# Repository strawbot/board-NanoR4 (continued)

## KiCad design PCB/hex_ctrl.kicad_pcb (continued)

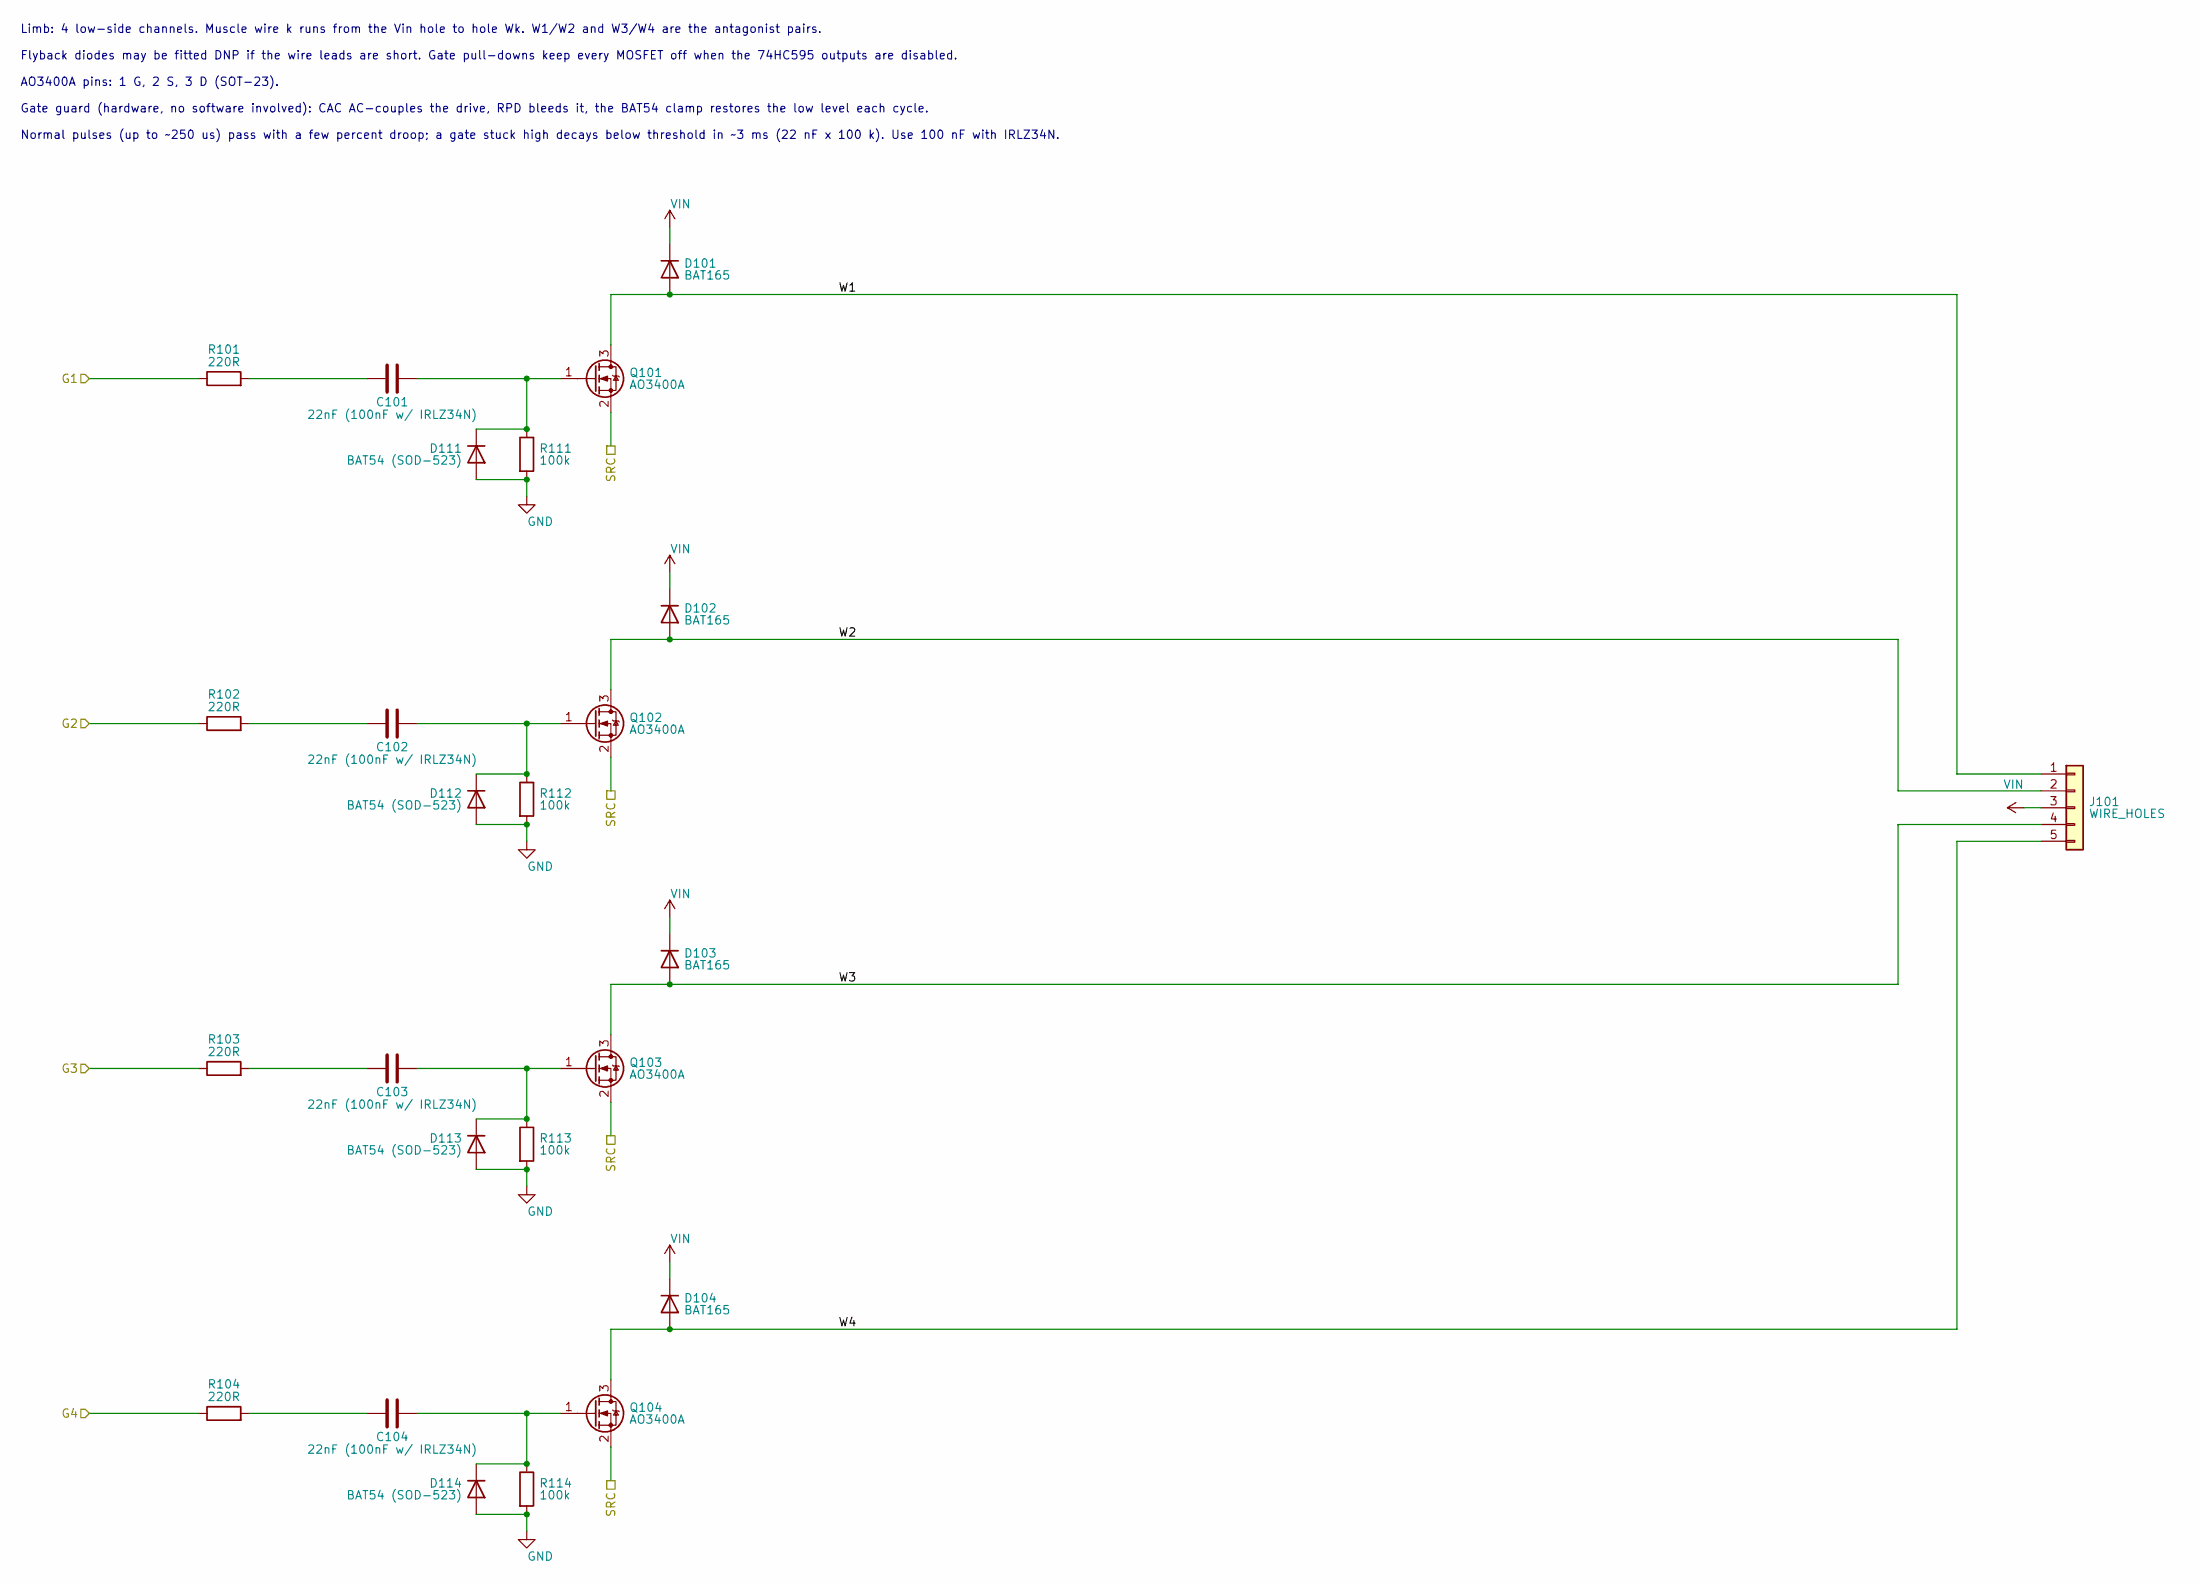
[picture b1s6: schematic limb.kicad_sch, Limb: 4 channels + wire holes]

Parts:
C101, C102, C103, C104: 22nF (100nF w/ IRLZ34N); C_0402_1005Metric
D101, D102, D103, D104: BAT165; D_SOD-323
D111, D112, D113, D114: BAT54 (SOD-523); D_SOD-523
J101: WIRE_HOLES; PinHeader_1x05_P2.54mm_Vertical
Q101, Q102, Q103, Q104: AO3400A; SOT-23
R101, R102, R103, R104: 220R; R_0402_1005Metric
R111, R112, R113, R114: 100k; R_0402_1005Metric

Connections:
/group_A/SRC: Q101.2 (S), Q102.2 (S), Q103.2 (S), Q104.2 (S); also elsewhere on the board
/group_A/limb_a/W1: D101.2 (A), J101.1, Q101.3 (D)
/group_A/limb_a/W2: D102.2 (A), J101.2, Q102.3 (D)
/group_A/limb_a/W3: D103.2 (A), J101.4, Q103.3 (D)
/group_A/limb_a/W4: D104.2 (A), J101.5, Q104.3 (D)
GND: D111.2 (A), D112.2 (A), D113.2 (A), D114.2 (A), R111.2, R112.2, R113.2, R114.2; also elsewhere on the board
G_A1: R101.1; also elsewhere on the board
G_A2: R102.1; also elsewhere on the board
G_A3: R103.1; also elsewhere on the board
G_A4: R104.1; also elsewhere on the board
unnamed: C101.1, R101.2
unnamed: C102.1, R102.2
unnamed: C103.1, R103.2
unnamed: C104.1, R104.2
unnamed: C101.2, D111.1 (K), Q101.1 (G), R111.1
unnamed: C102.2, D112.1 (K), Q102.1 (G), R112.1
unnamed: C103.2, D113.1 (K), Q103.1 (G), R113.1
unnamed: C104.2, D114.1 (K), Q104.1 (G), R114.1
VIN: D101.1 (K), D102.1 (K), D103.1 (K), D104.1 (K), J101.3; also elsewhere on the board

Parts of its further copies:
C201, C202, C203, C204, C301, C302, C303, C304, C401, C402, C403, C404, C501, C502, C503, C504, C601, C602, C603, C604: 22nF (100nF w/ IRLZ34N); C_0402_1005Metric
D201, D202, D203, D204, D301, D302, D303, D304, D401, D402, D403, D404, D501, D502, D503, D504, D601, D602, D603, D604: BAT165; D_SOD-323
D211, D212, D213, D214, D311, D312, D313, D314, D411, D412, D413, D414, D511, D512, D513, D514, D611, D612, D613, D614: BAT54 (SOD-523); D_SOD-523
J201, J301, J401, J501, J601: WIRE_HOLES; PinHeader_1x05_P2.54mm_Vertical
Q201, Q202, Q203, Q204, Q301, Q302, Q303, Q304, Q401, Q402, Q403, Q404, Q501, Q502, Q503, Q504, Q601, Q602, Q603, Q604: AO3400A; SOT-23
R201, R202, R203, R204, R301, R302, R303, R304, R401, R402, R403, R404, R501, R502, R503, R504, R601, R602, R603, R604: 220R; R_0402_1005Metric
R211, R212, R213, R214, R311, R312, R313, R314, R411, R412, R413, R414, R511, R512, R513, R514, R611, R612, R613, R614: 100k; R_0402_1005Metric

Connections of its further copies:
/group_A/SRC: Q201.2 (S), Q202.2 (S), Q203.2 (S), Q204.2 (S); also elsewhere on the board
/group_A/limb_b/W1: D201.2 (A), J201.1, Q201.3 (D)
/group_A/limb_b/W2: D202.2 (A), J201.2, Q202.3 (D)
/group_A/limb_b/W3: D203.2 (A), J201.4, Q203.3 (D)
/group_A/limb_b/W4: D204.2 (A), J201.5, Q204.3 (D)
/group_B/SRC: Q301.2 (S), Q302.2 (S), Q303.2 (S), Q304.2 (S), Q401.2 (S), Q402.2 (S), Q403.2 (S), Q404.2 (S); also elsewhere on the board
/group_B/limb_a/W1: D301.2 (A), J301.1, Q301.3 (D)
/group_B/limb_a/W2: D302.2 (A), J301.2, Q302.3 (D)
/group_B/limb_a/W3: D303.2 (A), J301.4, Q303.3 (D)
/group_B/limb_a/W4: D304.2 (A), J301.5, Q304.3 (D)
/group_B/limb_b/W1: D401.2 (A), J401.1, Q401.3 (D)
/group_B/limb_b/W2: D402.2 (A), J401.2, Q402.3 (D)
/group_B/limb_b/W3: D403.2 (A), J401.4, Q403.3 (D)
/group_B/limb_b/W4: D404.2 (A), J401.5, Q404.3 (D)
/group_C/SRC: Q501.2 (S), Q502.2 (S), Q503.2 (S), Q504.2 (S), Q601.2 (S), Q602.2 (S), Q603.2 (S), Q604.2 (S); also elsewhere on the board
/group_C/limb_a/W1: D501.2 (A), J501.1, Q501.3 (D)
/group_C/limb_a/W2: D502.2 (A), J501.2, Q502.3 (D)
/group_C/limb_a/W3: D503.2 (A), J501.4, Q503.3 (D)
/group_C/limb_a/W4: D504.2 (A), J501.5, Q504.3 (D)
/group_C/limb_b/W1: D601.2 (A), J601.1, Q601.3 (D)
/group_C/limb_b/W2: D602.2 (A), J601.2, Q602.3 (D)
/group_C/limb_b/W3: D603.2 (A), J601.4, Q603.3 (D)
/group_C/limb_b/W4: D604.2 (A), J601.5, Q604.3 (D)
GND: D211.2 (A), D212.2 (A), D213.2 (A), D214.2 (A), D311.2 (A), D312.2 (A), D313.2 (A), D314.2 (A), D411.2 (A), D412.2 (A), D413.2 (A), D414.2 (A), D511.2 (A), D512.2 (A), D513.2 (A), D514.2 (A), D611.2 (A), D612.2 (A), D613.2 (A), D614.2 (A), R211.2, R212.2, R213.2, R214.2, R311.2, R312.2, R313.2, R314.2, R411.2, R412.2, R413.2, R414.2, R511.2, R512.2, R513.2, R514.2, R611.2, R612.2, R613.2, R614.2; also elsewhere on the board
G_A5: R201.1; also elsewhere on the board
G_A6: R202.1; also elsewhere on the board
G_A7: R203.1; also elsewhere on the board
G_A8: R204.1; also elsewhere on the board
G_B1: R301.1; also elsewhere on the board
G_B2: R302.1; also elsewhere on the board
G_B3: R303.1; also elsewhere on the board
G_B4: R304.1; also elsewhere on the board
G_B5: R401.1; also elsewhere on the board
G_B6: R402.1; also elsewhere on the board
G_B7: R403.1; also elsewhere on the board
G_B8: R404.1; also elsewhere on the board
G_C1: R501.1; also elsewhere on the board
G_C2: R502.1; also elsewhere on the board
G_C3: R503.1; also elsewhere on the board
G_C4: R504.1; also elsewhere on the board
G_C5: R601.1; also elsewhere on the board
G_C6: R602.1; also elsewhere on the board
G_C7: R603.1; also elsewhere on the board
G_C8: R604.1; also elsewhere on the board
unnamed: C201.1, R201.2
unnamed: C202.1, R202.2
unnamed: C203.1, R203.2
unnamed: C204.1, R204.2
unnamed: C301.1, R301.2
unnamed: C302.1, R302.2
unnamed: C303.1, R303.2
unnamed: C304.1, R304.2
unnamed: C401.1, R401.2
unnamed: C402.1, R402.2
unnamed: C403.1, R403.2
unnamed: C404.1, R404.2
unnamed: C501.1, R501.2
unnamed: C502.1, R502.2
unnamed: C503.1, R503.2
unnamed: C504.1, R504.2
unnamed: C601.1, R601.2
unnamed: C602.1, R602.2
unnamed: C603.1, R603.2
unnamed: C604.1, R604.2
unnamed: C201.2, D211.1 (K), Q201.1 (G), R211.1
unnamed: C202.2, D212.1 (K), Q202.1 (G), R212.1
unnamed: C203.2, D213.1 (K), Q203.1 (G), R213.1
unnamed: C204.2, D214.1 (K), Q204.1 (G), R214.1
unnamed: C301.2, D311.1 (K), Q301.1 (G), R311.1
unnamed: C302.2, D312.1 (K), Q302.1 (G), R312.1
unnamed: C303.2, D313.1 (K), Q303.1 (G), R313.1
unnamed: C304.2, D314.1 (K), Q304.1 (G), R314.1
unnamed: C401.2, D411.1 (K), Q401.1 (G), R411.1
unnamed: C402.2, D412.1 (K), Q402.1 (G), R412.1
unnamed: C403.2, D413.1 (K), Q403.1 (G), R413.1
unnamed: C404.2, D414.1 (K), Q404.1 (G), R414.1
unnamed: C501.2, D511.1 (K), Q501.1 (G), R511.1
unnamed: C502.2, D512.1 (K), Q502.1 (G), R512.1
unnamed: C503.2, D513.1 (K), Q503.1 (G), R513.1
unnamed: C504.2, D514.1 (K), Q504.1 (G), R514.1
unnamed: C601.2, D611.1 (K), Q601.1 (G), R611.1
unnamed: C602.2, D612.1 (K), Q602.1 (G), R612.1
unnamed: C603.2, D613.1 (K), Q603.1 (G), R613.1
unnamed: C604.2, D614.1 (K), Q604.1 (G), R614.1
VIN: D201.1 (K), D202.1 (K), D203.1 (K), D204.1 (K), D301.1 (K), D302.1 (K), D303.1 (K), D304.1 (K), D401.1 (K), D402.1 (K), D403.1 (K), D404.1 (K), D501.1 (K), D502.1 (K), D503.1 (K), D504.1 (K), D601.1 (K), D602.1 (K), D603.1 (K), D604.1 (K), J201.3, J301.3, J401.3, J501.3, J601.3; also elsewhere on the board

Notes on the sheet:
Limb: 4 low-side channels. Muscle wire k runs from the Vin hole to hole Wk. W1/W2 and W3/W4 are the antagonist pairs.
Flyback diodes may be fitted DNP if the wire leads are short. Gate pull-downs keep every MOSFET off when the 74HC595 outputs are disabled.
AO3400A pins: 1 G, 2 S, 3 D (SOT-23).
Gate guard (hardware, no software involved): CAC AC-couples the drive, RPD bleeds it, the BAT54 clamp restores the low level each cycle.
Normal pulses (up to ~250 us) pass with a few percent droop; a gate stuck high decays below threshold in ~3 ms (22 nF x 100 k). Use 100 nF with IRLZ34N.

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
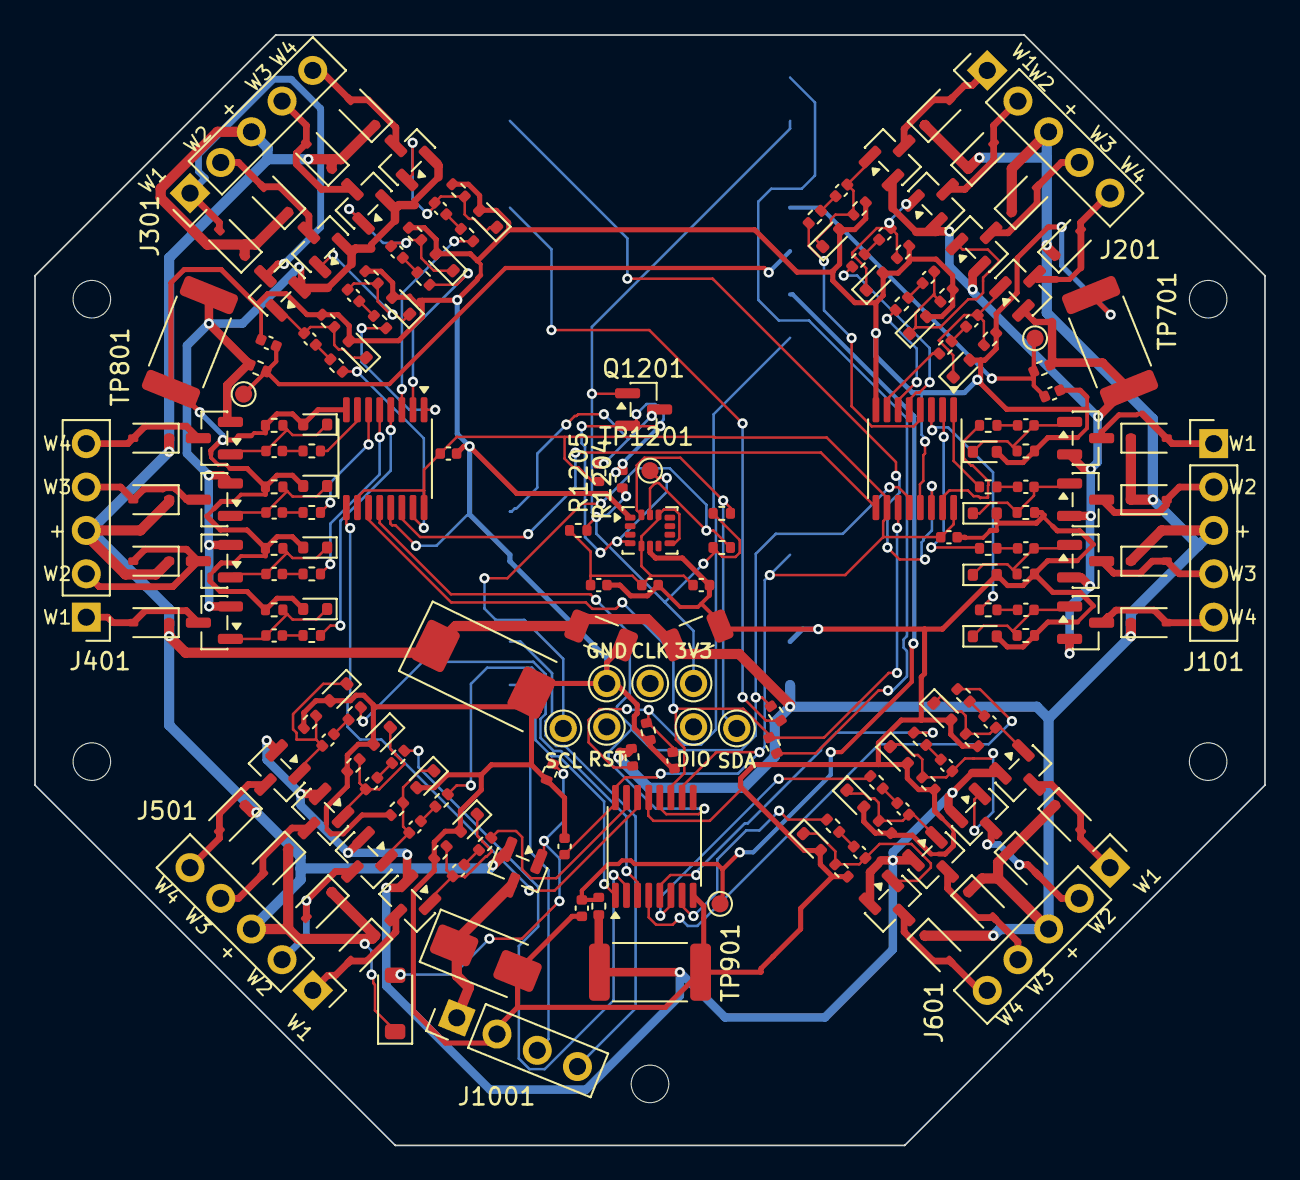
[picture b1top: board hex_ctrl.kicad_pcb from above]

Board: 2 copper layers, 72.0 x 65.0 mm, 205 parts (1 on the bottom side), 123 nets.
